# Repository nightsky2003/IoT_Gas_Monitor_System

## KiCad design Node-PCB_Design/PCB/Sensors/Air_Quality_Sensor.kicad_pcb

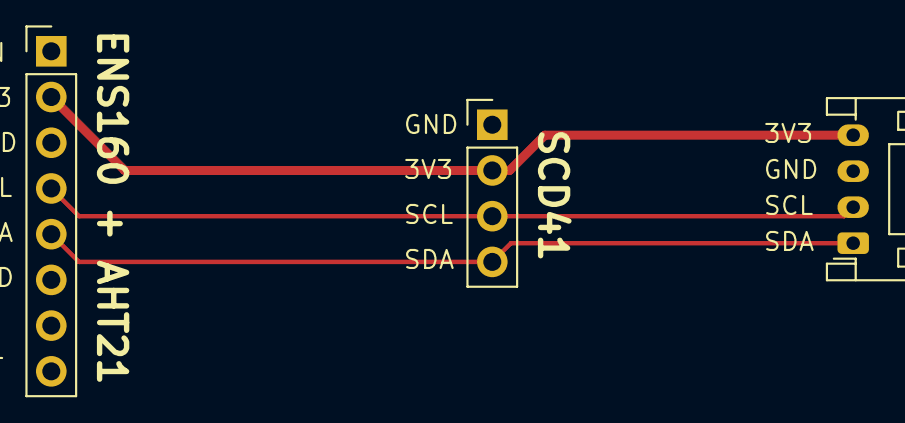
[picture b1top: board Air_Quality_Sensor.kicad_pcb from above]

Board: 2 copper layers, 3 parts (0 on the bottom side), 4 nets.

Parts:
J1: Conn_01x04; JST_PH_S4B-PH-K_1x04_P2.00mm_Horizontal
U1: SCD41; PinHeader_1x04_P2.54mm_Vertical
U2: ENS160+AHT21; PinHeader_1x08_P2.54mm_Vertical

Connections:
+3V3: J1.4, U1.2 (VCC), U2.2 (3V3)
/SCL: J1.2, U1.3 (SCL), U2.4 (SCL)
/SDA: J1.1, U1.4 (SDA), U2.5 (SDA)
GND: J1.3, U1.1 (GND), U2.3 (GND)

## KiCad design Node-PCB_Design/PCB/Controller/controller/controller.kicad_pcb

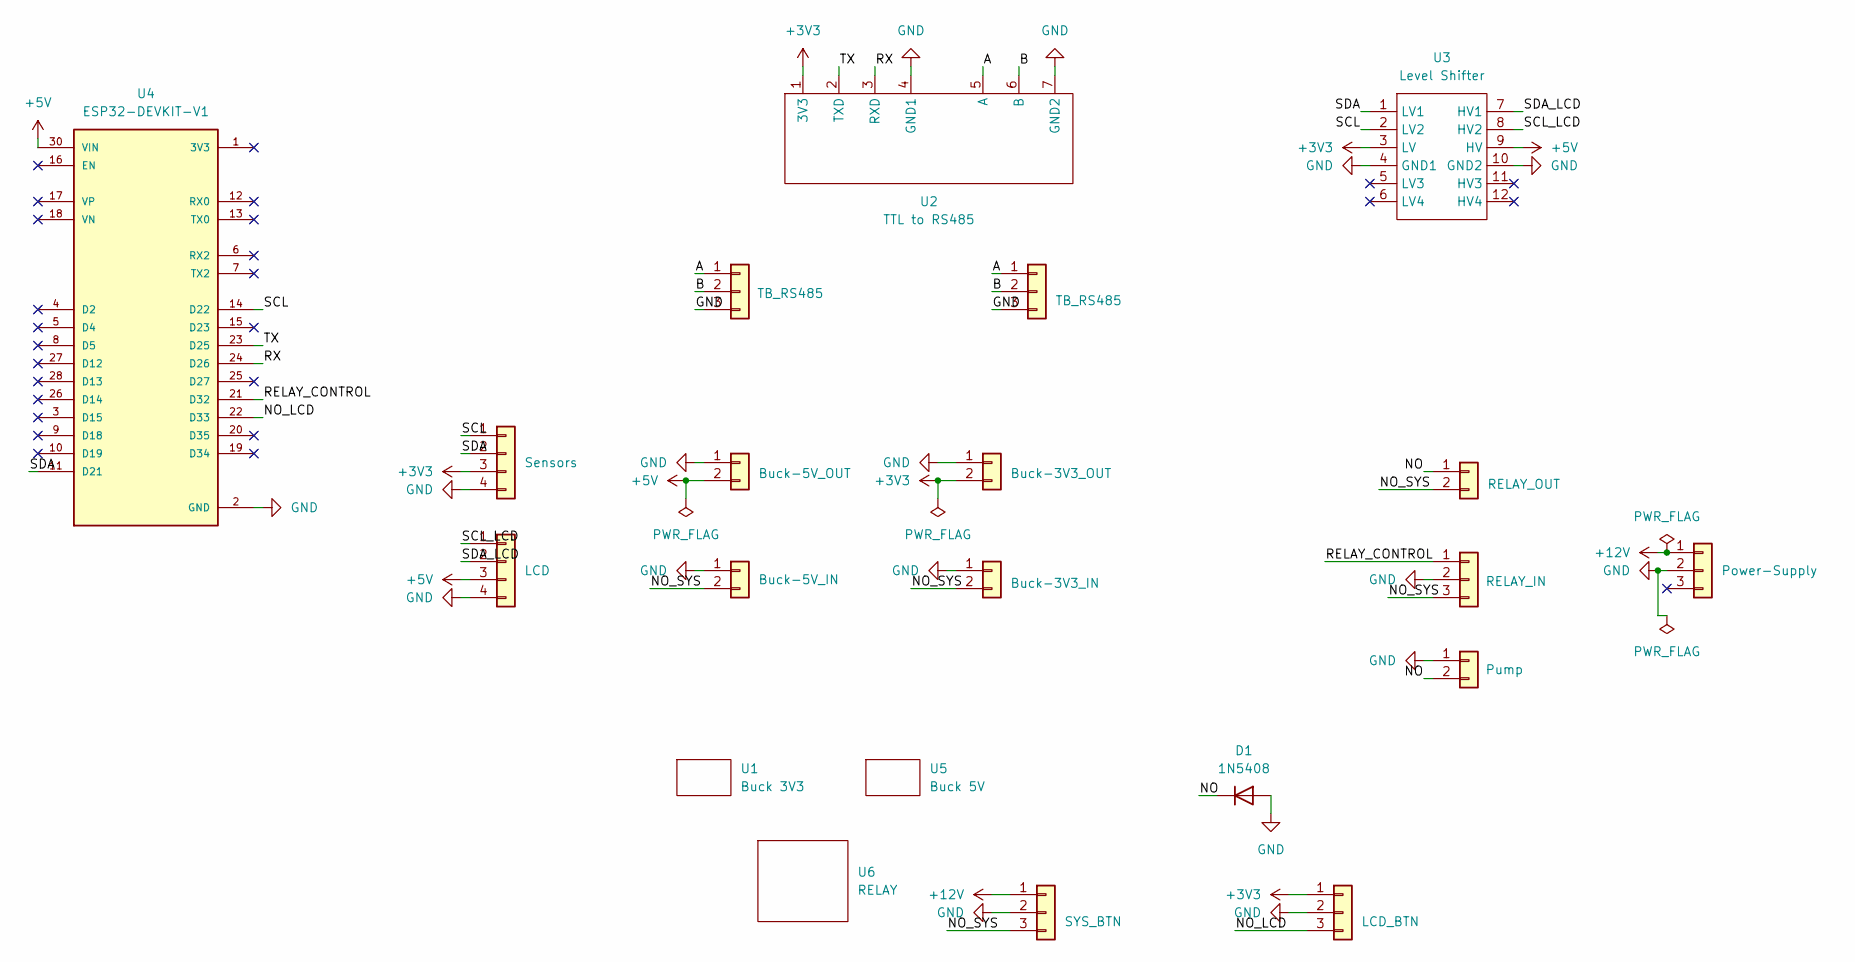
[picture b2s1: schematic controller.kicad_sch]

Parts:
D1: 1N5408; D_DO-201AD_P15.24mm_Horizontal
J1: Power-Supply; BarrelJack_Horizontal
J2: RELAY_IN; JST_PH_B3B-PH-K_1x03_P2.00mm_Vertical
J3: RELAY_OUT; JST_VH_B2P-VH_1x02_P3.96mm_Vertical
J4: Buck-3V3_IN; JST_PH_B2B-PH-K_1x02_P2.00mm_Vertical
J5: Buck-3V3_OUT; JST_PH_B2B-PH-K_1x02_P2.00mm_Vertical
J6: Buck-5V_IN; JST_PH_B2B-PH-K_1x02_P2.00mm_Vertical
J7: Buck-5V_OUT; JST_PH_B2B-PH-K_1x02_P2.00mm_Vertical
J8: Pump; JST_VH_B2P-VH_1x02_P3.96mm_Vertical
J9: Sensors; JST_PH_B4B-PH-K_1x04_P2.00mm_Vertical
J10: LCD; JST_PH_B4B-PH-K_1x04_P2.00mm_Vertical
J11, J12: TB_RS485; TerminalBlock_Phoenix_MKDS-1,5-3-5.08_1x03_P5.08mm_Horizont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
J13: SYS_BTN; JST_VH_B3P-VH_1x03_P3.96mm_Vertical
J14: LCD_BTN; JST_PH_B3B-PH-K_1x03_P2.00mm_Vertical
U1: Buck 3V3; Buck
U2: TTL to RS485; TTL_to_RS485
U3: Level Shifter; Level shifter
U4: ESP32-DEVKIT-V1; MODULE_ESP32_DEVKIT_V1; PARTREV N/A
U5: Buck 5V; Buck
U6: RELAY

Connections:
+3V3: J5.2, J9.3, J14.1, U2.1 (3V3), U3.3 (LV)
+5V: J7.2, J10.3, U3.9 (HV), U4.30 (VIN)
+12V: J1.1, J13.1
/A: J11.1, J12.1, U2.5 (A)
/B: J11.2, J12.2, U2.6 (B)
/NO: D1.1 (K), J3.1, J8.2
/NO_LCD: J14.3, U4.22 (D33)
/NO_SYS: J2.3, J3.2, J4.2, J6.2, J13.3
/RELAY_CONTROL: J2.1, U4.21 (D32)
/RX: U2.3 (RXD), U4.24 (D26)
/SCL: J9.1, U3.2 (LV2), U4.14 (D22)
/SCL_LCD: J10.1, U3.8 (HV2)
/SDA: J9.2, U3.1 (LV1), U4.11 (D21)
/SDA_LCD: J10.2, U3.7 (HV1)
/TX: U2.2 (TXD), U4.23 (D25)
GND: D1.2 (A), J1.2, J2.2, J4.1, J5.1, J6.1, J7.1, J8.1, J9.4, J10.4, J11.3, J12.3, J13.2, J14.2, U2.4 (GND1), U2.7 (GND2), U3.4 (GND1), U3.10 (GND2), U4.2 (GND), U4.29 (GND)

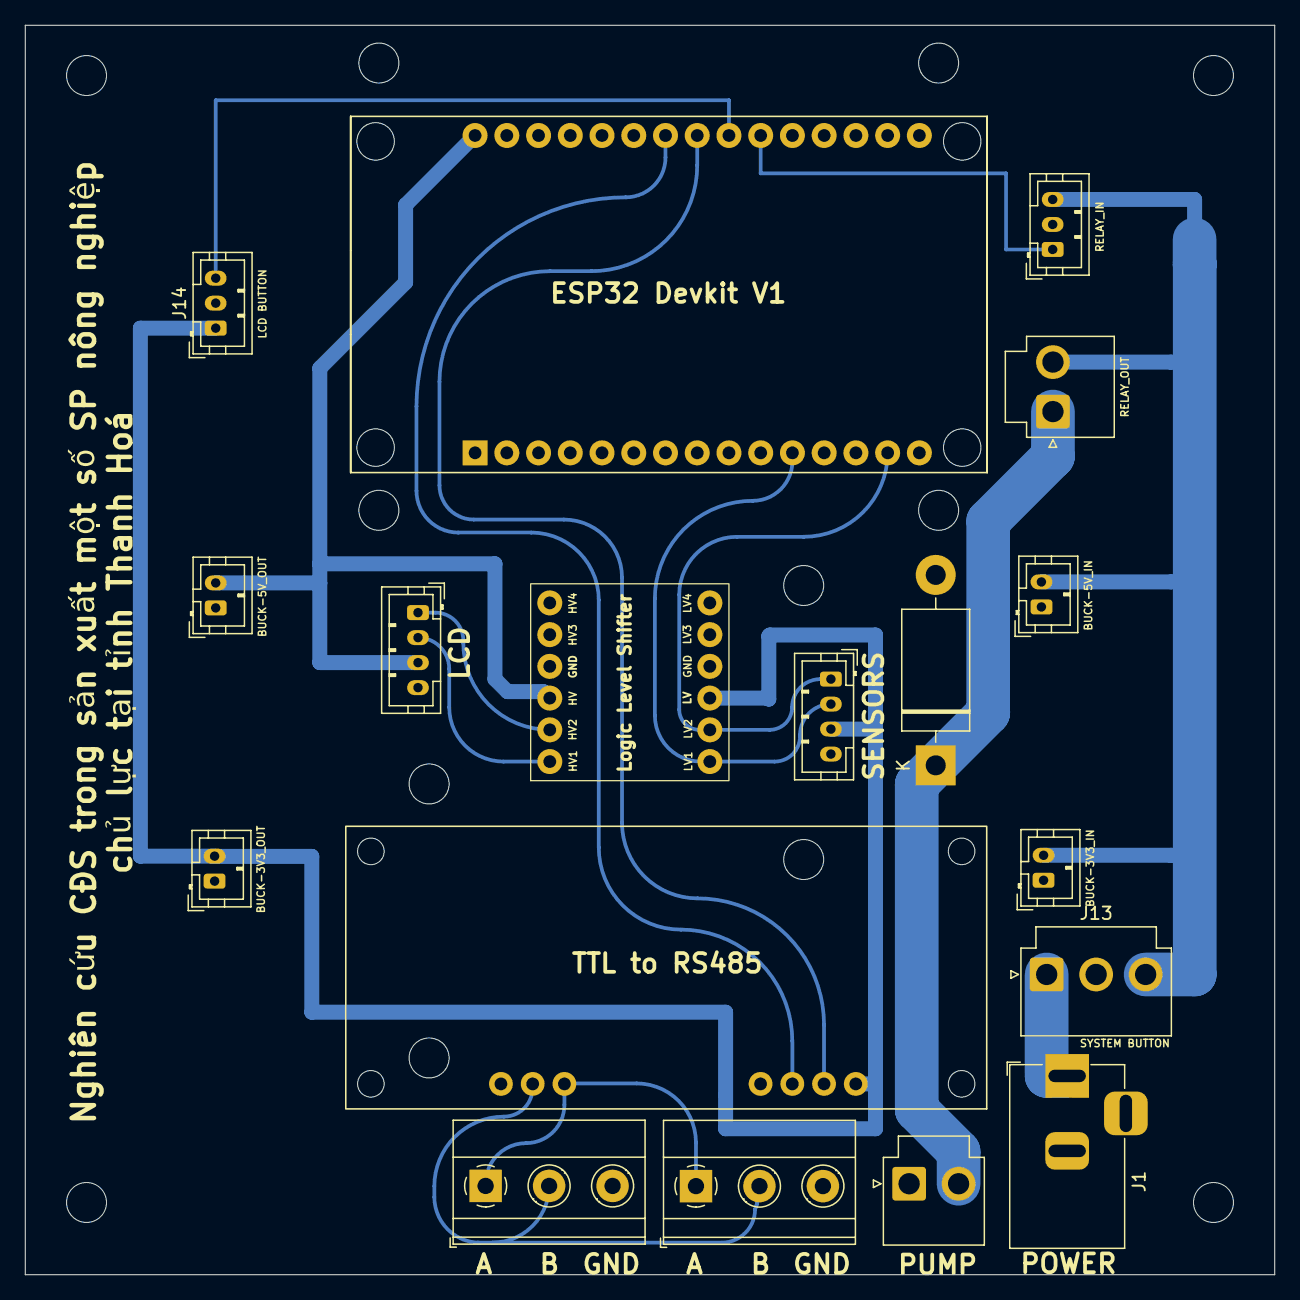
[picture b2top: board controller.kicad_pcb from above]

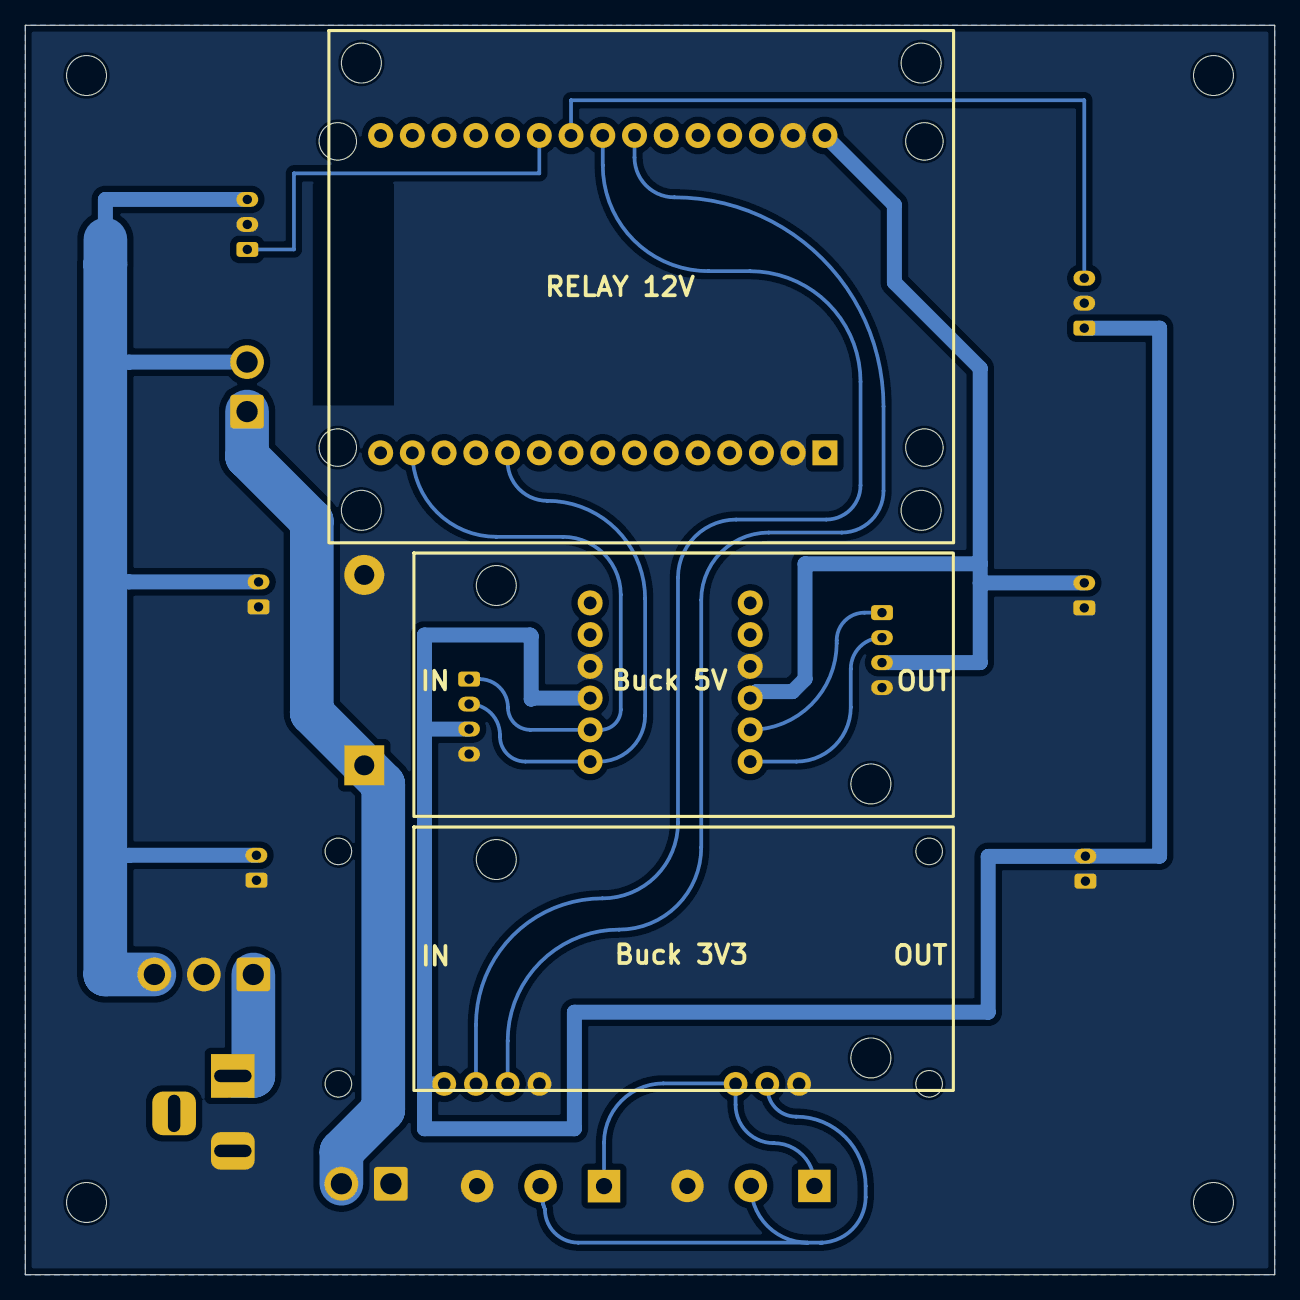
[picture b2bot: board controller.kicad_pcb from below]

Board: 2 copper layers, 100.0 x 100.0 mm, 21 parts (3 on the bottom side), 16 nets.

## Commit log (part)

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2026-04-25 latest
